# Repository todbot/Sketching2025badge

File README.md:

# Sketching2025badge

Badge for Sketching in Hardware 2025

# Features

- Three (3) capacitive touch pads
- Nine (9) "Neopixel"-compatible side-light RGB LEDs that shine through the back
- Four (4) sewable connectors: V+, Gnd, TX (PB2), and RX (PB3)
- One status LED on back of board
- Standard SAO pinout w/ I2C. Spare GPIO lines wired to UART TX/RX
- ATtiny816-based, same as [seesaw boards](https://learn.adafruit.com/adafruit-attiny817-seesaw)
- Easy compilation using standard Ardiuno toolchain and [megaTinyCore](https://github.com/SpenceKonde/megaTinyCore)
- Programmable with UDPI with a [USB-Serial adapter](https://amzn.to/3IKpMry)
- Uses modified [TouchyTouch](https://github.com/todbot/TouchyTouch) captouch library, included

# ATtiny816 pins used

|    Use              | GPIO   | Arduino pin |
|---------------------|--------|-------------|
| Status LED          | PB4    | 5           |
| Neopixel LEDs       | PC2    | 12          |
| Touch pad 0         | PA6    | 0           |
| Touch pad 1         | PA5    | 1           |
| Touch pad 2         | PA4    | 2           |
| SAO I2C SCL         | PB0    | 9           |
| SAO I2C SDA         | PB1    | 8           |
| Sew / SAO UART TX   | PB2    | 7           |
| Sew / SAO UART RX   | PB3    | 6           |

# Reprogramming the badge

The default firmware is a fun little demo. But you can extend or replace it.

For details see [docs/firmware-install.md](docs/firmware-install.md)

But basically:
- Open up Arduino, add http://drazzy.com/package_drazzy.com_index.json
to the Board Manager URLs in Settings.
- Load "firmware/Sketching2025badge_attiny816/Sketching2025badge_attiny816.ino"
- Set the chip & programmer settings as in firmware-install.md
- Upload code with "Sketch" -> "Upload Using Programmer"

# Protective "Backer"

Since the LEDs and MCU on the back don't have the protection of the battery
holders as standoffs, a 3d-printed "backer" is included with the badge.
It snaps onto the badge using the sewable holes.
It can be removed by lifting it out, if you want to sew the badge down or
otherwise use the sewable holes.

See the "enclosure" directory for STEP/STL to print your own.

# Demos

* 30Aug2025 - Prototyp0 PCBA w/ batts on face, from JLC (with oops mask hole in center)

  https://github.com/user-attachments/assets/092c7233-f480-4e2a-861c-cc95c8bd24c3

# Renders

* 1 Oct 2025 - production version

* 16Aug2025 - Render0 - refaced TouchWheelSAO, basic graphics layout on 100mm (4") circular PCB, all components on back, routing incomplete

  https://github.com/user-attachments/assets/017a1953-9797-4b04-9c11-582e099e5368

* 16Aug2026 - Render0a - same as above, but with AAA holders on top

  https://github.com/user-attachments/assets/b0e8170d-4cca-4846-9cb0-e9c19dae7c72

# Schematic

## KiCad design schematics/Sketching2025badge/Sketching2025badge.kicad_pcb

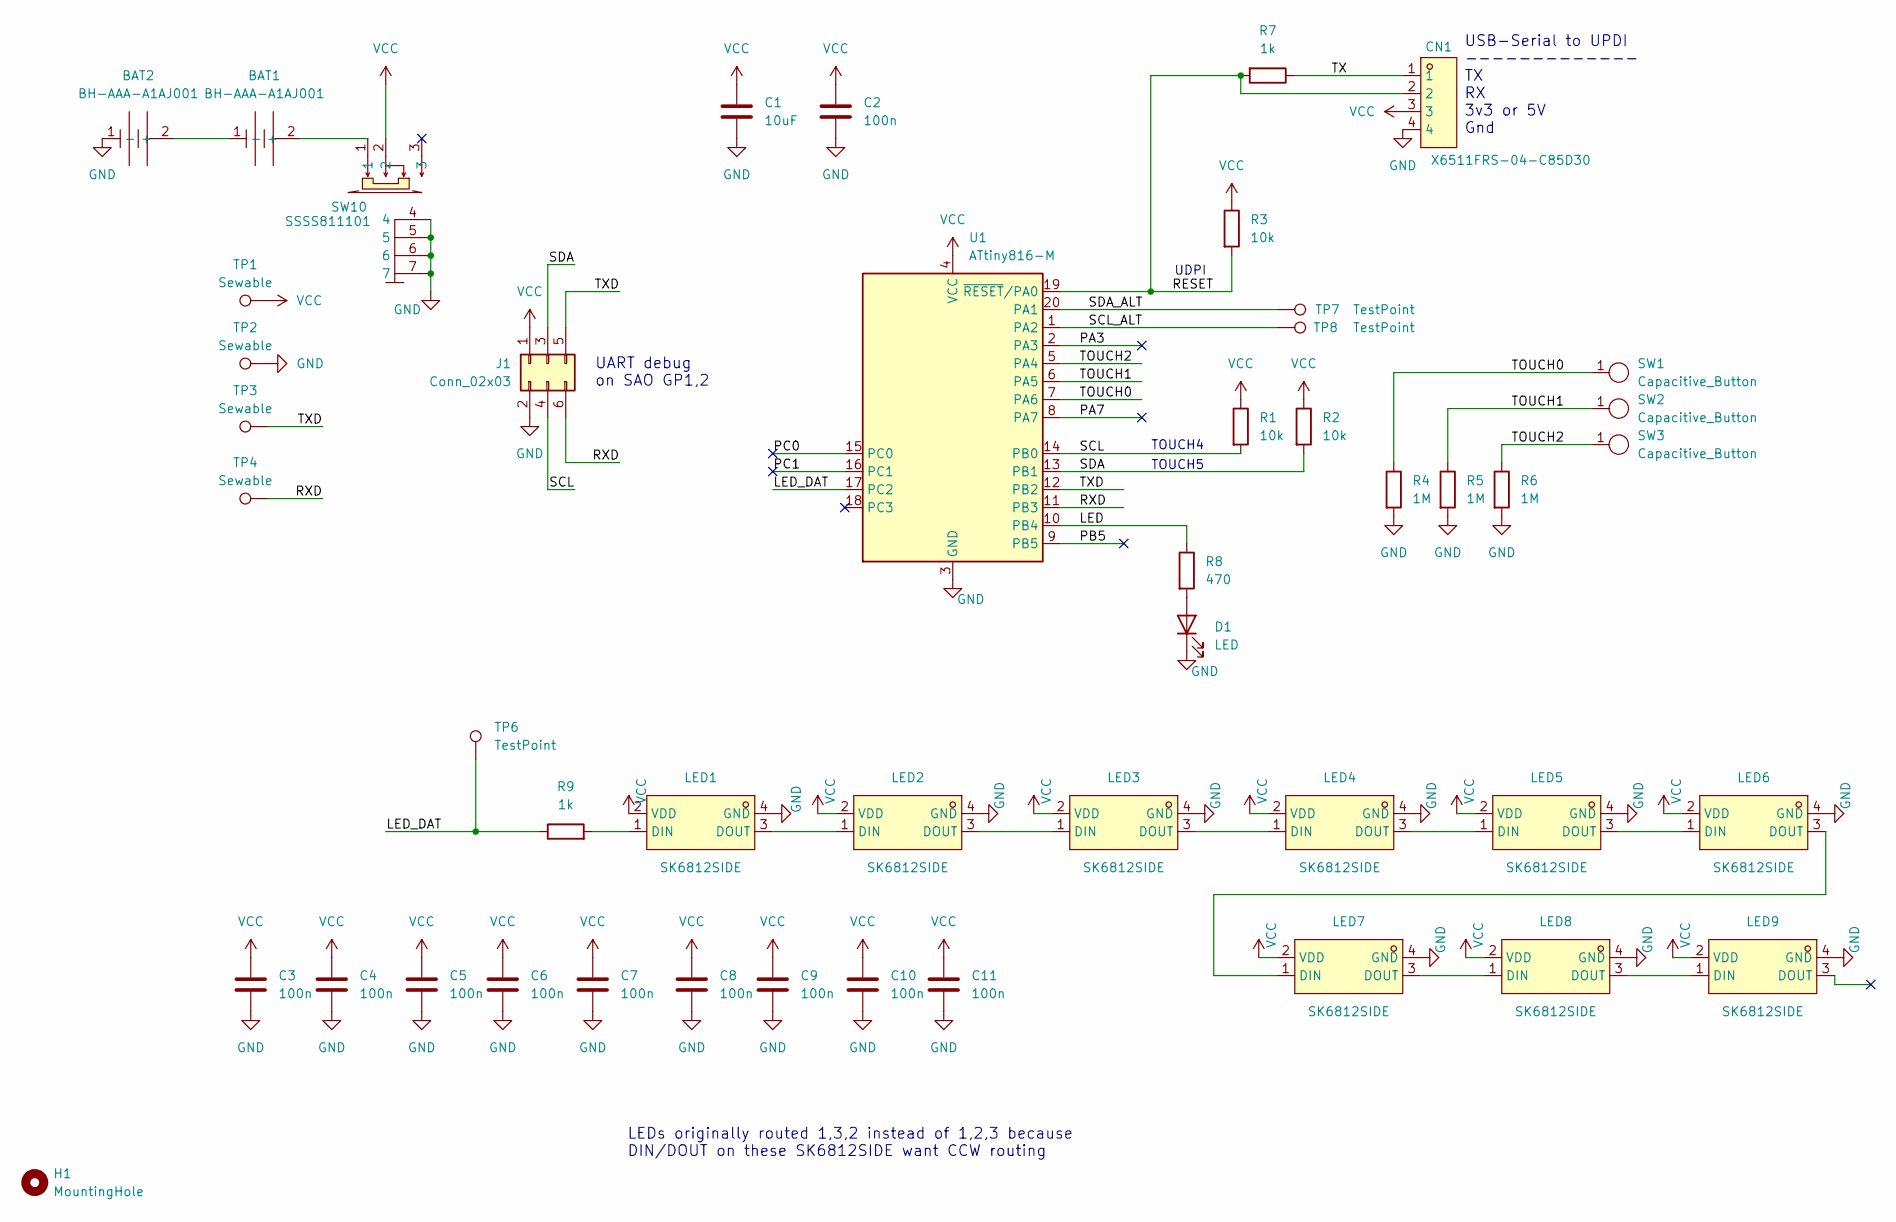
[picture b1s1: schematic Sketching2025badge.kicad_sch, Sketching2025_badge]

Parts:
BAT1, BAT2: BH-AAA-A1AJ001; BAT-TH_BH-AAA-A1AJ001; LCSC Part C5290189
C1: 10uF; R_0603_1608Metric; LCSC Part C434425
C2, C3, C4, C5, C6, C7, C8, C9, C10, C11: 100n; R_0603_1608Metric; LCSC Part C1590
CN1: X6511FRS-04-C85D30; HDR-SMD_4P-P2.54-H-F; LCSC Part C5142237
D1: LED; LED_0603_1608Metric; LCSC Part C434425
H1: MountingHole; MountingHole_6.4mm_M6
J1: Conn_02x03; PinSocket_2x03_P2.54mm_Vertical; Part Number LL1009-2A, 2.54MM 2*3PIN HEADER,LENGTH=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; LCSC Part C541853
LED1, LED2, LED3, LED4, LED5, LED6, LED7, LED8, LED9: SK6812SIDE; LED-SMD_4P-L4.0-W1.6-L; LCSC Part C5378721
R1, R2, R3: 10k; R_0603_1608Metric
R4, R5, R6: 1M; R_0603_1608Metric
R7, R9: 1k; R_0603_1608Metric
R8: 470; R_0603_1608Metric
SW1, SW2, SW3: Capacitive_Button; Pad-CapTouch-10mm-roundrect-nosilk
SW10: SSSS811101; SW-SMD_SSSS811101; LCSC Part C109335
TP1, TP2, TP3, TP4: Sewable; Lilypad-BUTTONHOLE
TP6, TP7, TP8: TestPoint; TestPoint_Pad_D1.5mm
U1: ATtiny816-M; UQFN-20_L3.0-W3.0-P0.40-BL-EP1.7; LCSC Part C2052778

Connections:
/LED: R8.1, U1.10 (PB4)
/LED_DAT: R9.1, TP6.1, U1.17 (PC2)
/PA3: U1.2 (PA3)
/PA7: U1.8 (PA7)
/PB5: U1.9 (PB5)
/PC0: U1.15 (PC0)
/PC1: U1.16 (PC1)
/RESET: CN1.2, R3.2, R7.2, U1.19 (~RESET/PA0)
/RXD: J1.6 (GND), TP4.1, U1.11 (PB3)
/SCL: J1.4 (GND), R1.2, U1.14 (PB0)
/SCL_ALT: TP8.1, U1.1 (PA2)
/SDA: J1.3 (GND), R2.2, U1.13 (PB1)
/SDA_ALT: TP7.1, U1.20 (PA1)
/TOUCH0: R4.1, SW1.1 (A), U1.7 (PA6)
/TOUCH1: R5.1, SW2.1 (A), U1.6 (PA5)
/TOUCH2: R6.1, SW3.1 (A), U1.5 (PA4)
/TX: CN1.1, R7.1
/TXD: J1.5 (GND), TP3.1, U1.12 (PB2)
GND: BAT2.1 (-), C1.2, C2.2, C3.2, C4.2, C5.2, C6.2, C7.2, C8.2, C9.2, C10.2, C11.2, CN1.4, D1.1 (K), J1.2 (+12V), LED1.4 (GND), LED2.4 (GND), LED3.4 (GND), LED4.4 (GND), LED5.4 (GND), LED6.4 (GND), LED7.4 (GND), LED8.4 (GND), LED9.4 (GND), R4.2, R5.2, R6.2, SW10.4, SW10.5, SW10.6, SW10.7, TP2.1, U1.3 (GND), U1.21 (GND)
unnamed: BAT1.2 (+), SW10.1
unnamed: BAT1.1 (-), BAT2.2 (+)
unnamed: D1.2 (A), R8.2
unnamed: LED1.1 (DIN), R9.2
unnamed: LED1.3 (DOUT), LED2.1 (DIN)
unnamed: LED2.3 (DOUT), LED3.1 (DIN)
unnamed: LED3.3 (DOUT), LED4.1 (DIN)
unnamed: LED4.3 (DOUT), LED5.1 (DIN)
unnamed: LED5.3 (DOUT), LED6.1 (DIN)
unnamed: LED6.3 (DOUT), LED7.1 (DIN)
unnamed: LED7.3 (DOUT), LED8.1 (DIN)
unnamed: LED8.3 (DOUT), LED9.1 (DIN)
VCC: C1.1, C2.1, C3.1, C4.1, C5.1, C6.1, C7.1, C8.1, C9.1, C10.1, C11.1, CN1.3, J1.1 (+12V), LED1.2 (VDD), LED2.2 (VDD), LED3.2 (VDD), LED4.2 (VDD), LED5.2 (VDD), LED6.2 (VDD), LED7.2 (VDD), LED8.2 (VDD), LED9.2 (VDD), R1.1, R2.1, R3.1, SW10.2, TP1.1, U1.4 (VCC)

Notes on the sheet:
LEDs originally routed 1,3,2 instead of 1,2,3 because DIN/DOUT on these SK6812SIDE want CCW routing
TOUCH5
TOUCH4
UART debug on SAO GP1,2
USB-Serial to UPDI ------------- TX RX 3v3 or 5V Gnd
UDPI

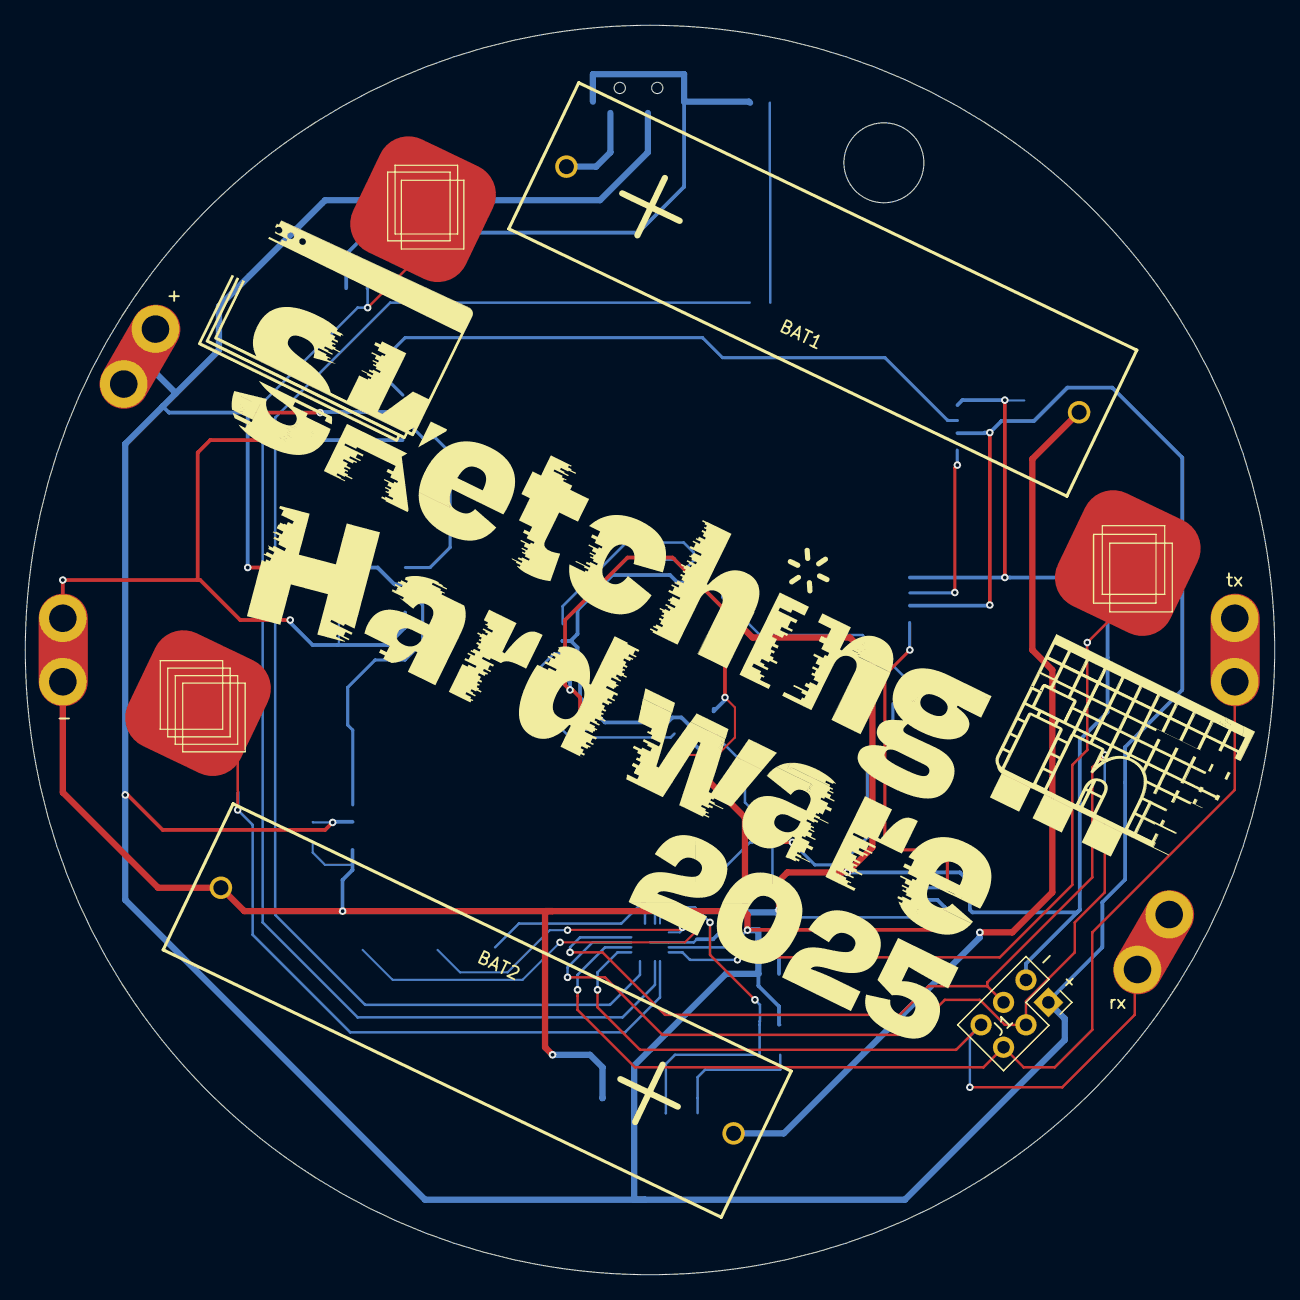
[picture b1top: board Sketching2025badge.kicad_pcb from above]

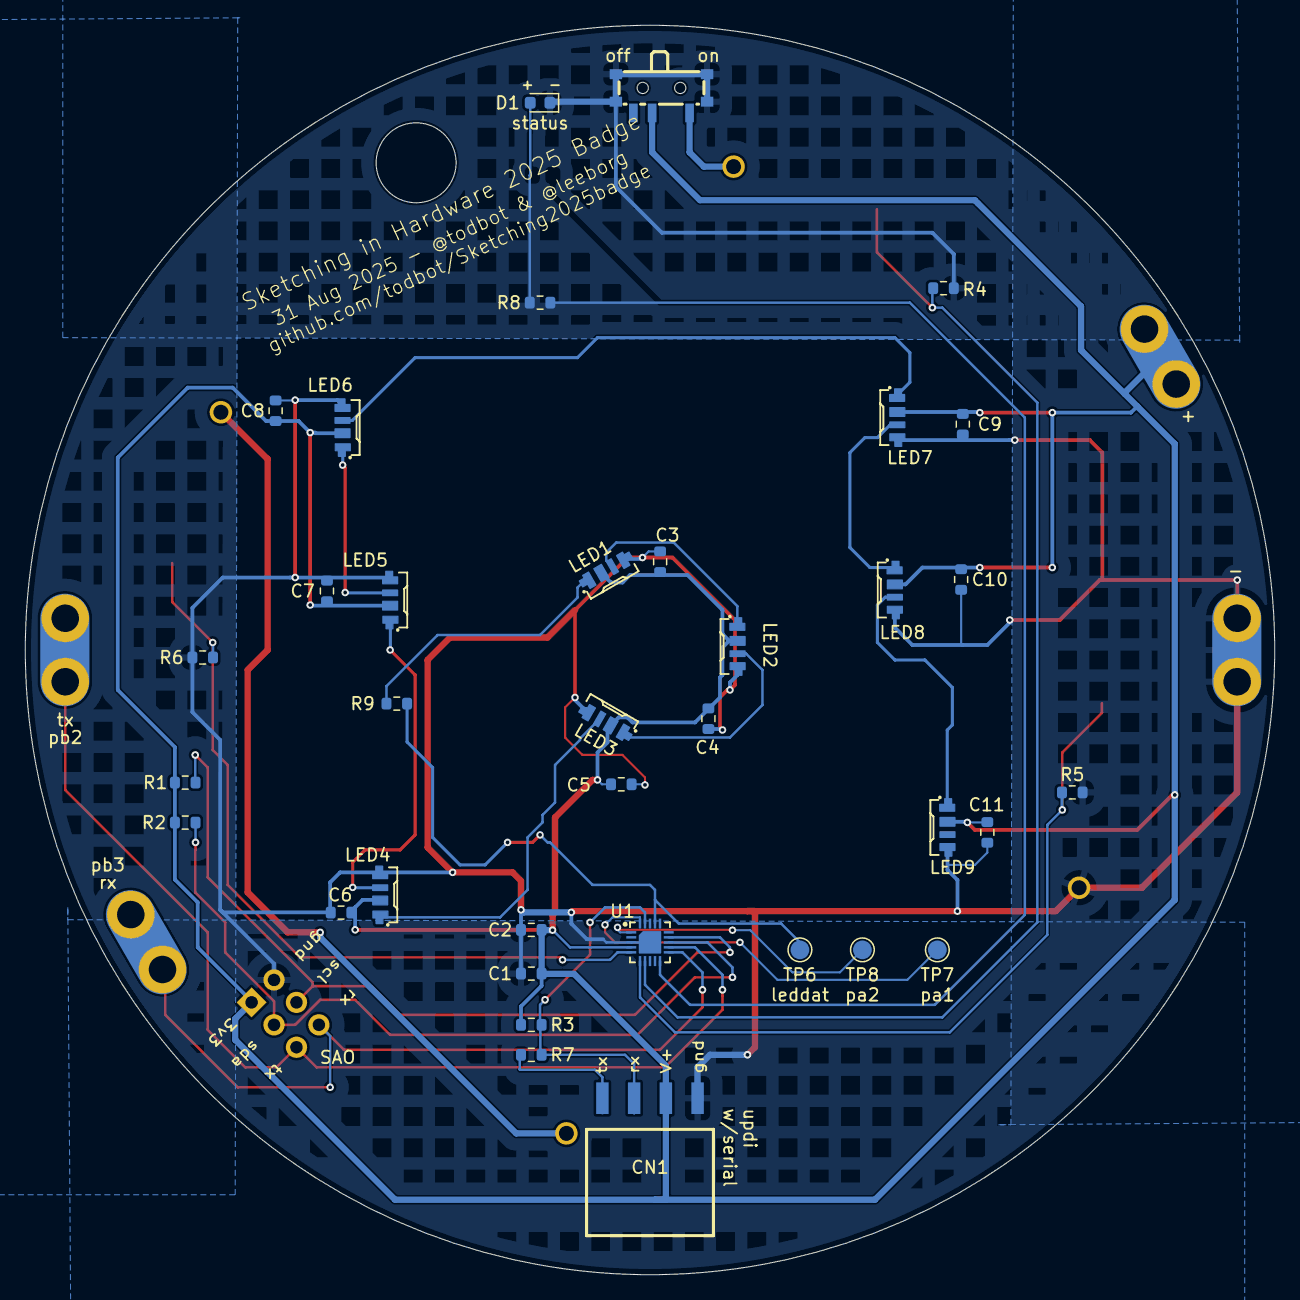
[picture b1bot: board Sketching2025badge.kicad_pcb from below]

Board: 2 copper layers, 100.0 x 100.0 mm, 47 parts (40 on the bottom side), 27 nets.

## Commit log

2025-08-16 first
2025-08-21 almost routed, difficult getting through the maze of the B.Mask
2025-08-22 first version routed, not pass drc yet
2025-08-22 routed, mostly pass drc
2025-08-24 added bypass caps and switch
2025-08-24 first version to production
2025-08-30 verify jlc test run1
2025-08-31 moved to female prog header, widened mask polygons for more light
2025-08-31 code as in the demo0 video
2025-08-31 docs
2025-08-31 Update README.md with prototype0 demo video
2025-08-31 minor fixups to pcb
2025-09-01 more docs
2025-09-01 update with prelim version sent to PCBWay
2025-09-01 example code cleanup
2025-09-02 update docs
2025-09-25 cleanup and fixes
2025-09-27 tune batch programming info
2025-09-27 trying to do something interesting with this badge
2025-09-29 final firmware I guess
2025-09-29 add backing STL and STEP
2025-09-29 allow PORT to be set for batch programming
2025-10-05 update readme and notes
2025-10-05 update notes
2025-10-10 Add demo image and programming section to README
    Added a demo image and a new section for programming instructions.
2025-10-10 Document Arduino-CLI installation process
    Added section for Arduino-CLI installation as an alternative to Arduino IDE.
2025-10-10 add programming pic
2025-10-10 Update firmware-install.md with images
    Removed placeholder image and added actual images for programming setup.
2025-10-11 add abbreviated install instructions
2025-10-12 update backer readme bit
